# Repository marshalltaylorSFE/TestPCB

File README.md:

# TestPCB
Repo for various eagle projects

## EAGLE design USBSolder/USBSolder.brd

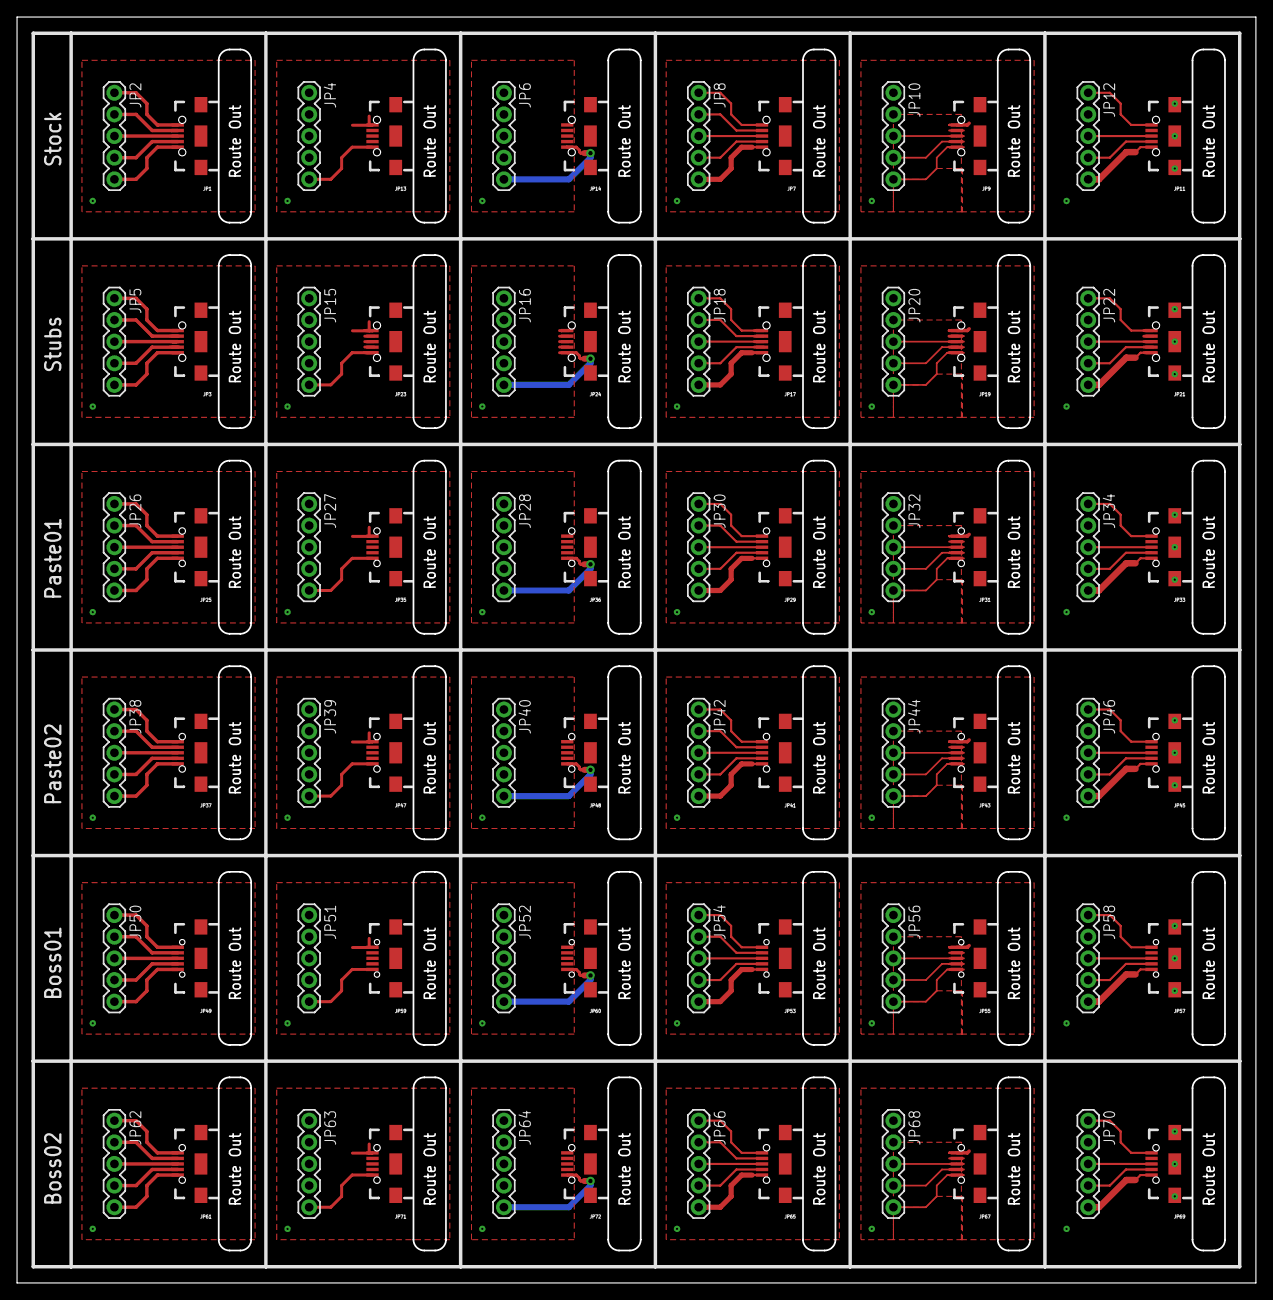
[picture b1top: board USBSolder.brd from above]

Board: 2 copper layers, 145.4 x 148.6 mm, 73 parts (0 on the bottom side), 108 nets.

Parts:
FRAME1: FRAME-LETTER; CREATIVE_COMMONS
JP1, JP7, JP9, JP11, JP13, JP14: USB-B-MICRO-SMD_V03
JP2, JP4, JP5, JP6, JP8, JP10, JP12, JP15, JP16, JP18, JP20, JP22, JP26, JP27, JP28, JP30, JP32, JP34, JP38, JP39, JP40, JP42, JP44, JP46, JP50, JP51, JP52, JP54, JP56, JP58, JP62, JP63, JP64, JP66, JP68, JP70: 1X05
JP3, JP17, JP19, JP21, JP23, JP24: USB-MICRO-STUBS-01
JP25, JP29, JP31, JP33, JP35, JP36: USB-MICRO-PASTE-01
JP37, JP41, JP43, JP45, JP47, JP48: USB-MICRO-PASTE-02
JP49, JP53, JP55, JP57, JP59, JP60: USB-MICRO-BOSS-01
JP61, JP65, JP67, JP69, JP71, JP72: USB-MICRO-BOSS-02

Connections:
5V1: JP6.5, JP14.VBUS1
5V2: JP16.5, JP24.VBUS1
5V3: JP28.5, JP36.VBUS1
5V4: JP40.5, JP48.VBUS1
5V5: JP52.5, JP60.VBUS1
5V6: JP64.5, JP72.VBUS1
GND: JP1.SHIELD1, JP1.SHIELD2, JP1.SHIELD3, JP4.1, JP6.1, JP7.GND1, JP8.1, JP9.GND1, JP10.1, JP11.GND1, JP11.SHIELD1, JP11.SHIELD2, JP11.SHIELD3, JP12.1, JP13.GND1, JP14.GND1
GND1: JP3.SHIELD1, JP3.SHIELD2, JP3.SHIELD3, JP15.1, JP16.1, JP17.GND1, JP18.1, JP19.GND1, JP20.1, JP21.GND1, JP21.SHIELD1, JP21.SHIELD2, JP21.SHIELD3, JP22.1, JP23.GND1, JP24.GND1
GND2: JP25.SHIELD1, JP25.SHIELD2, JP25.SHIELD3, JP27.1, JP28.1, JP29.GND1, JP30.1, JP31.GND1, JP32.1, JP33.GND1, JP33.SHIELD1, JP33.SHIELD2, JP33.SHIELD3, JP34.1, JP35.GND1, JP36.GND1
GND3: JP37.SHIELD1, JP37.SHIELD2, JP37.SHIELD3, JP39.1, JP40.1, JP41.GND1, JP42.1, JP43.GND1, JP44.1, JP45.GND1, JP45.SHIELD1, JP45.SHIELD2, JP45.SHIELD3, JP46.1, JP47.GND1, JP48.GND1
GND4: JP49.SHIELD1, JP49.SHIELD2, JP49.SHIELD3, JP51.1, JP52.1, JP53.GND1, JP54.1, JP55.GND1, JP56.1, JP57.GND1, JP57.SHIELD1, JP57.SHIELD2, JP57.SHIELD3, JP58.1, JP59.GND1, JP60.GND1
GND5: JP61.SHIELD1, JP61.SHIELD2, JP61.SHIELD3, JP63.1, JP64.1, JP65.GND1, JP66.1, JP67.GND1, JP68.1, JP69.GND1, JP69.SHIELD1, JP69.SHIELD2, JP69.SHIELD3, JP70.1, JP71.GND1, JP72.GND1
unnamed: JP1.GND1, JP2.1
unnamed: JP1.ID1, JP2.2
unnamed: JP1.D+1, JP2.3
unnamed: JP1.D-1, JP2.4
unnamed: JP1.VBUS1, JP2.5
unnamed: JP3.GND1, JP5.1
unnamed: JP3.ID1, JP5.2
unnamed: JP7.ID1, JP8.2
unnamed: JP4.5, JP13.VBUS1
unnamed: JP7.D+1, JP8.3
unnamed: JP7.D-1, JP8.4
unnamed: JP7.VBUS1, JP8.5
unnamed: JP3.D+1, JP5.3
unnamed: JP3.D-1, JP5.4
unnamed: JP9.D+1, JP10.3
unnamed: JP9.D-1, JP10.4
unnamed: JP9.VBUS1, JP10.5
unnamed: JP3.VBUS1, JP5.5
unnamed: JP15.5, JP23.VBUS1
unnamed: JP11.D+1, JP12.3
unnamed: JP11.D-1, JP12.4
unnamed: JP11.VBUS1, JP12.5
unnamed: JP17.ID1, JP18.2
unnamed: JP17.D+1, JP18.3
unnamed: JP17.D-1, JP18.4
unnamed: JP17.VBUS1, JP18.5
unnamed: JP19.D+1, JP20.3
unnamed: JP19.D-1, JP20.4
unnamed: JP19.VBUS1, JP20.5
unnamed: JP21.D+1, JP22.3
unnamed: JP21.D-1, JP22.4
unnamed: JP21.VBUS1, JP22.5
unnamed: JP25.GND1, JP26.1
unnamed: JP25.ID1, JP26.2
unnamed: JP25.D+1, JP26.3
unnamed: JP25.D-1, JP26.4
unnamed: JP25.VBUS1, JP26.5
unnamed: JP27.5, JP35.VBUS1
unnamed: JP29.ID1, JP30.2
unnamed: JP29.D+1, JP30.3
unnamed: JP29.D-1, JP30.4
unnamed: JP29.VBUS1, JP30.5
unnamed: JP31.D+1, JP32.3
unnamed: JP31.D-1, JP32.4
unnamed: JP31.VBUS1, JP32.5
unnamed: JP33.D+1, JP34.3
unnamed: JP33.D-1, JP34.4
unnamed: JP33.VBUS1, JP34.5
unnamed: JP37.GND1, JP38.1
unnamed: JP37.ID1, JP38.2
unnamed: JP37.D+1, JP38.3
unnamed: JP37.D-1, JP38.4
unnamed: JP37.VBUS1, JP38.5
unnamed: JP39.5, JP47.VBUS1
unnamed: JP41.ID1, JP42.2
unnamed: JP41.D+1, JP42.3
unnamed: JP41.D-1, JP42.4
unnamed: JP41.VBUS1, JP42.5
unnamed: JP43.D+1, JP44.3
unnamed: JP43.D-1, JP44.4
unnamed: JP43.VBUS1, JP44.5
unnamed: JP45.D+1, JP46.3
unnamed: JP45.D-1, JP46.4
unnamed: JP45.VBUS1, JP46.5
unnamed: JP49.GND1, JP50.1
unnamed: JP49.ID1, JP50.2
unnamed: JP49.D+1, JP50.3
unnamed: JP49.D-1, JP50.4
unnamed: JP49.VBUS1, JP50.5
unnamed: JP51.5, JP59.VBUS1
unnamed: JP53.ID1, JP54.2
unnamed: JP53.D+1, JP54.3
unnamed: JP53.D-1, JP54.4
unnamed: JP53.VBUS1, JP54.5
unnamed: JP55.D+1, JP56.3
unnamed: JP55.D-1, JP56.4
unnamed: JP55.VBUS1, JP56.5
unnamed: JP57.D+1, JP58.3
unnamed: JP57.D-1, JP58.4
unnamed: JP57.VBUS1, JP58.5
unnamed: JP61.GND1, JP62.1
unnamed: JP61.ID1, JP62.2
unnamed: JP61.D+1, JP62.3
unnamed: JP61.D-1, JP62.4
unnamed: JP61.VBUS1, JP62.5
unnamed: JP63.5, JP71.VBUS1
unnamed: JP65.ID1, JP66.2
unnamed: JP65.D+1, JP66.3
unnamed: JP65.D-1, JP66.4
unnamed: JP65.VBUS1, JP66.5
unnamed: JP67.D+1, JP68.3
unnamed: JP67.D-1, JP68.4
unnamed: JP67.VBUS1, JP68.5
unnamed: JP69.D+1, JP70.3
unnamed: JP69.D-1, JP70.4
unnamed: JP69.VBUS1, JP70.5

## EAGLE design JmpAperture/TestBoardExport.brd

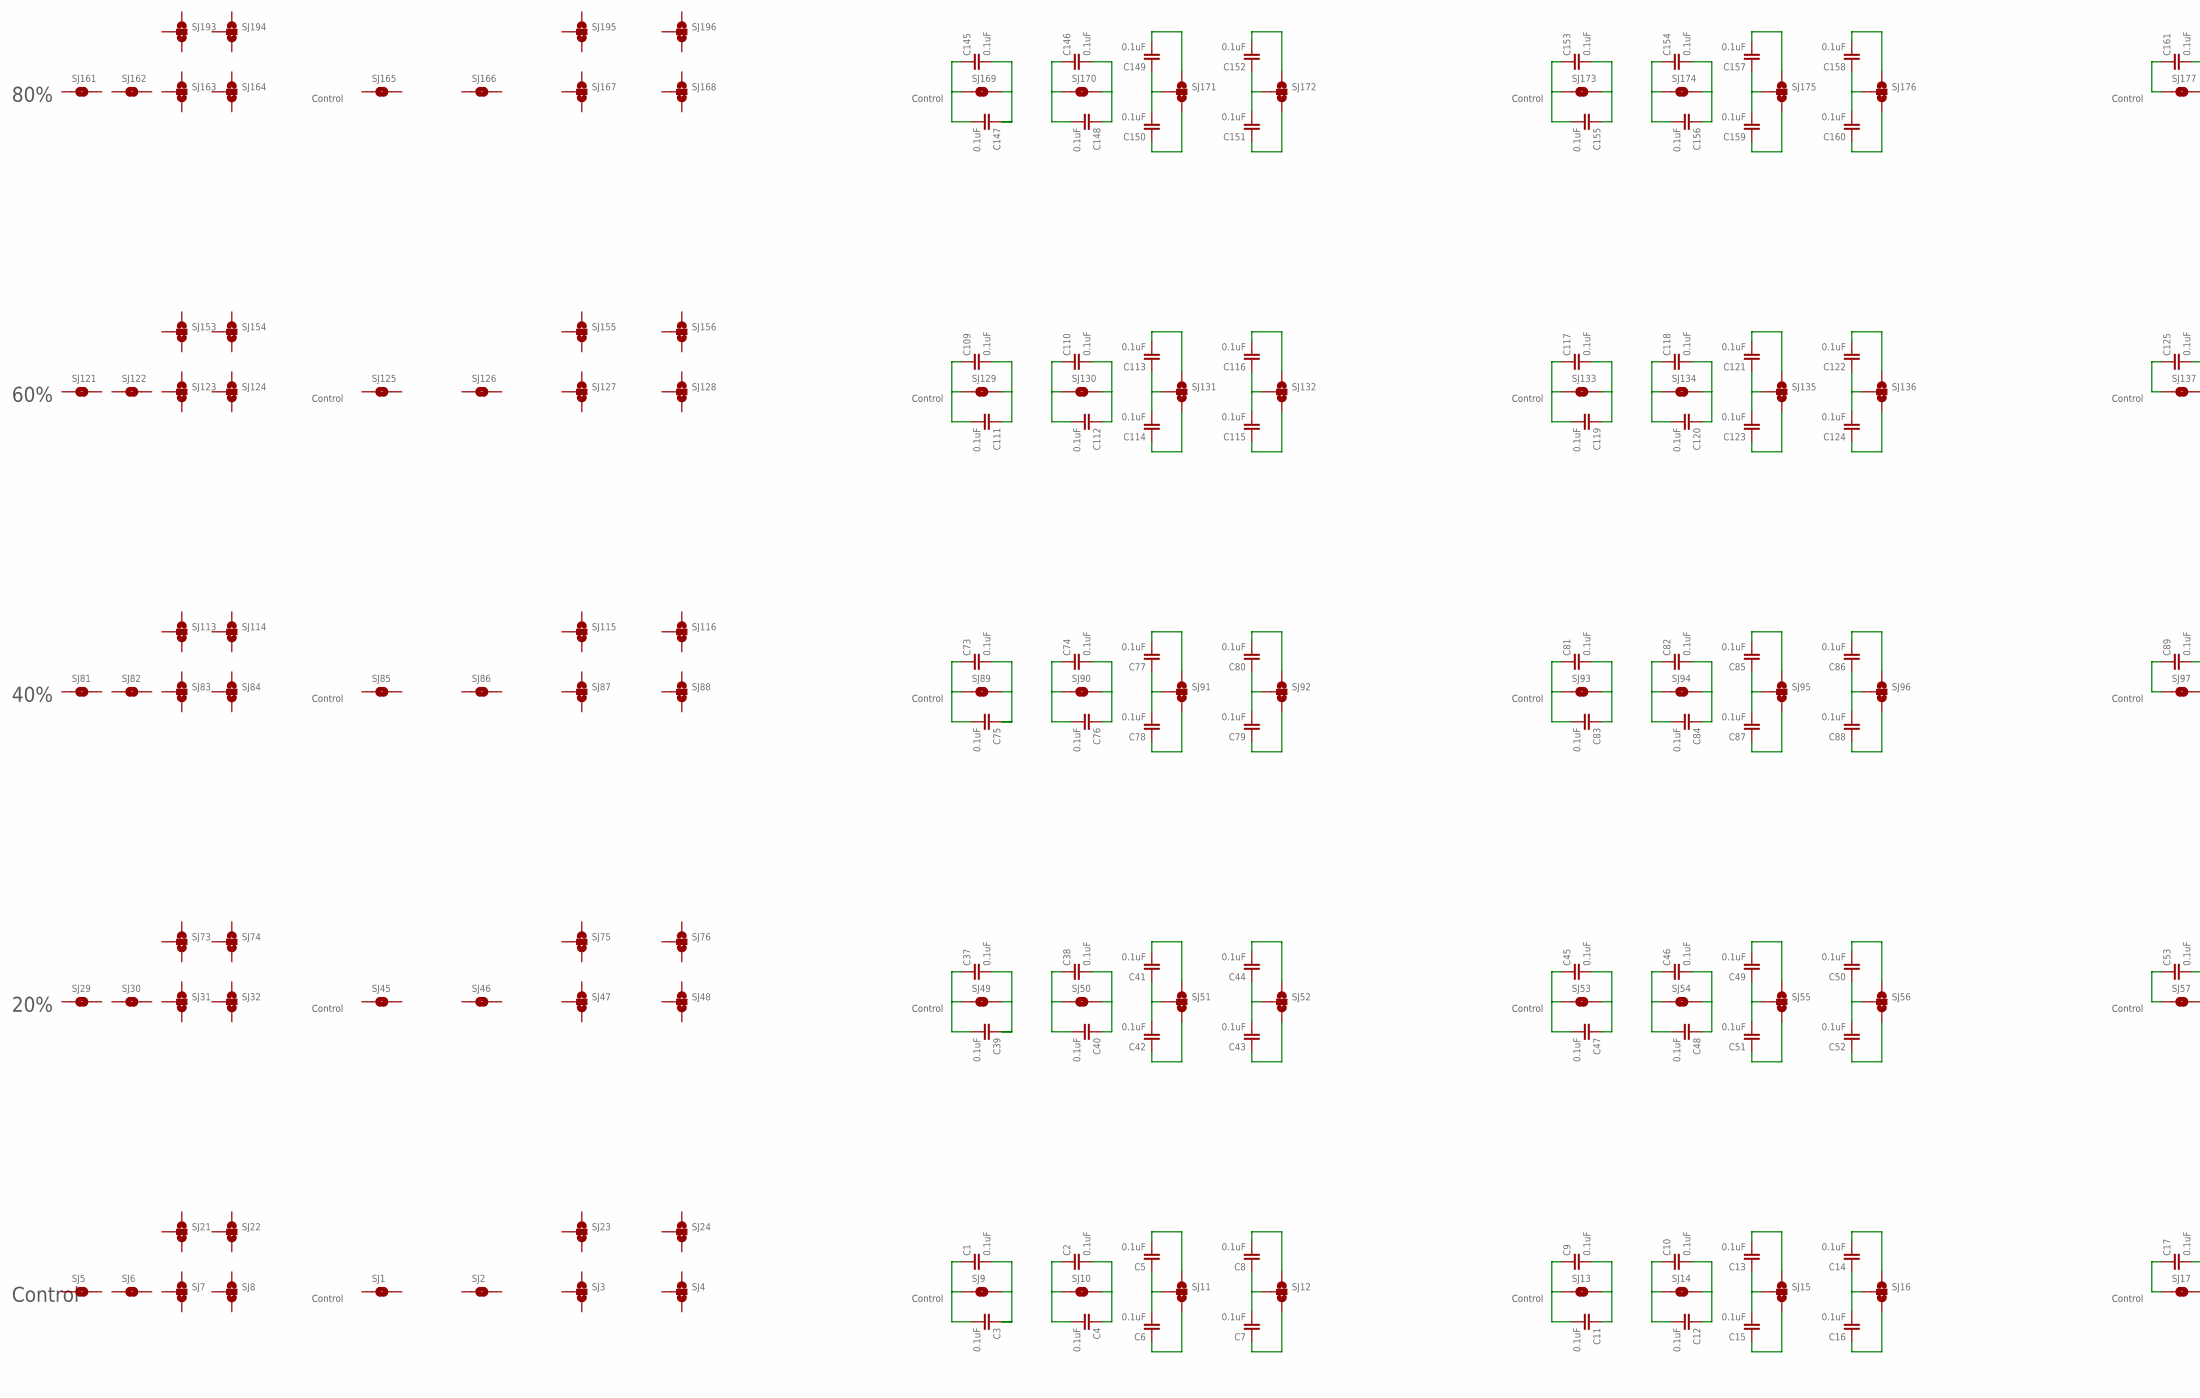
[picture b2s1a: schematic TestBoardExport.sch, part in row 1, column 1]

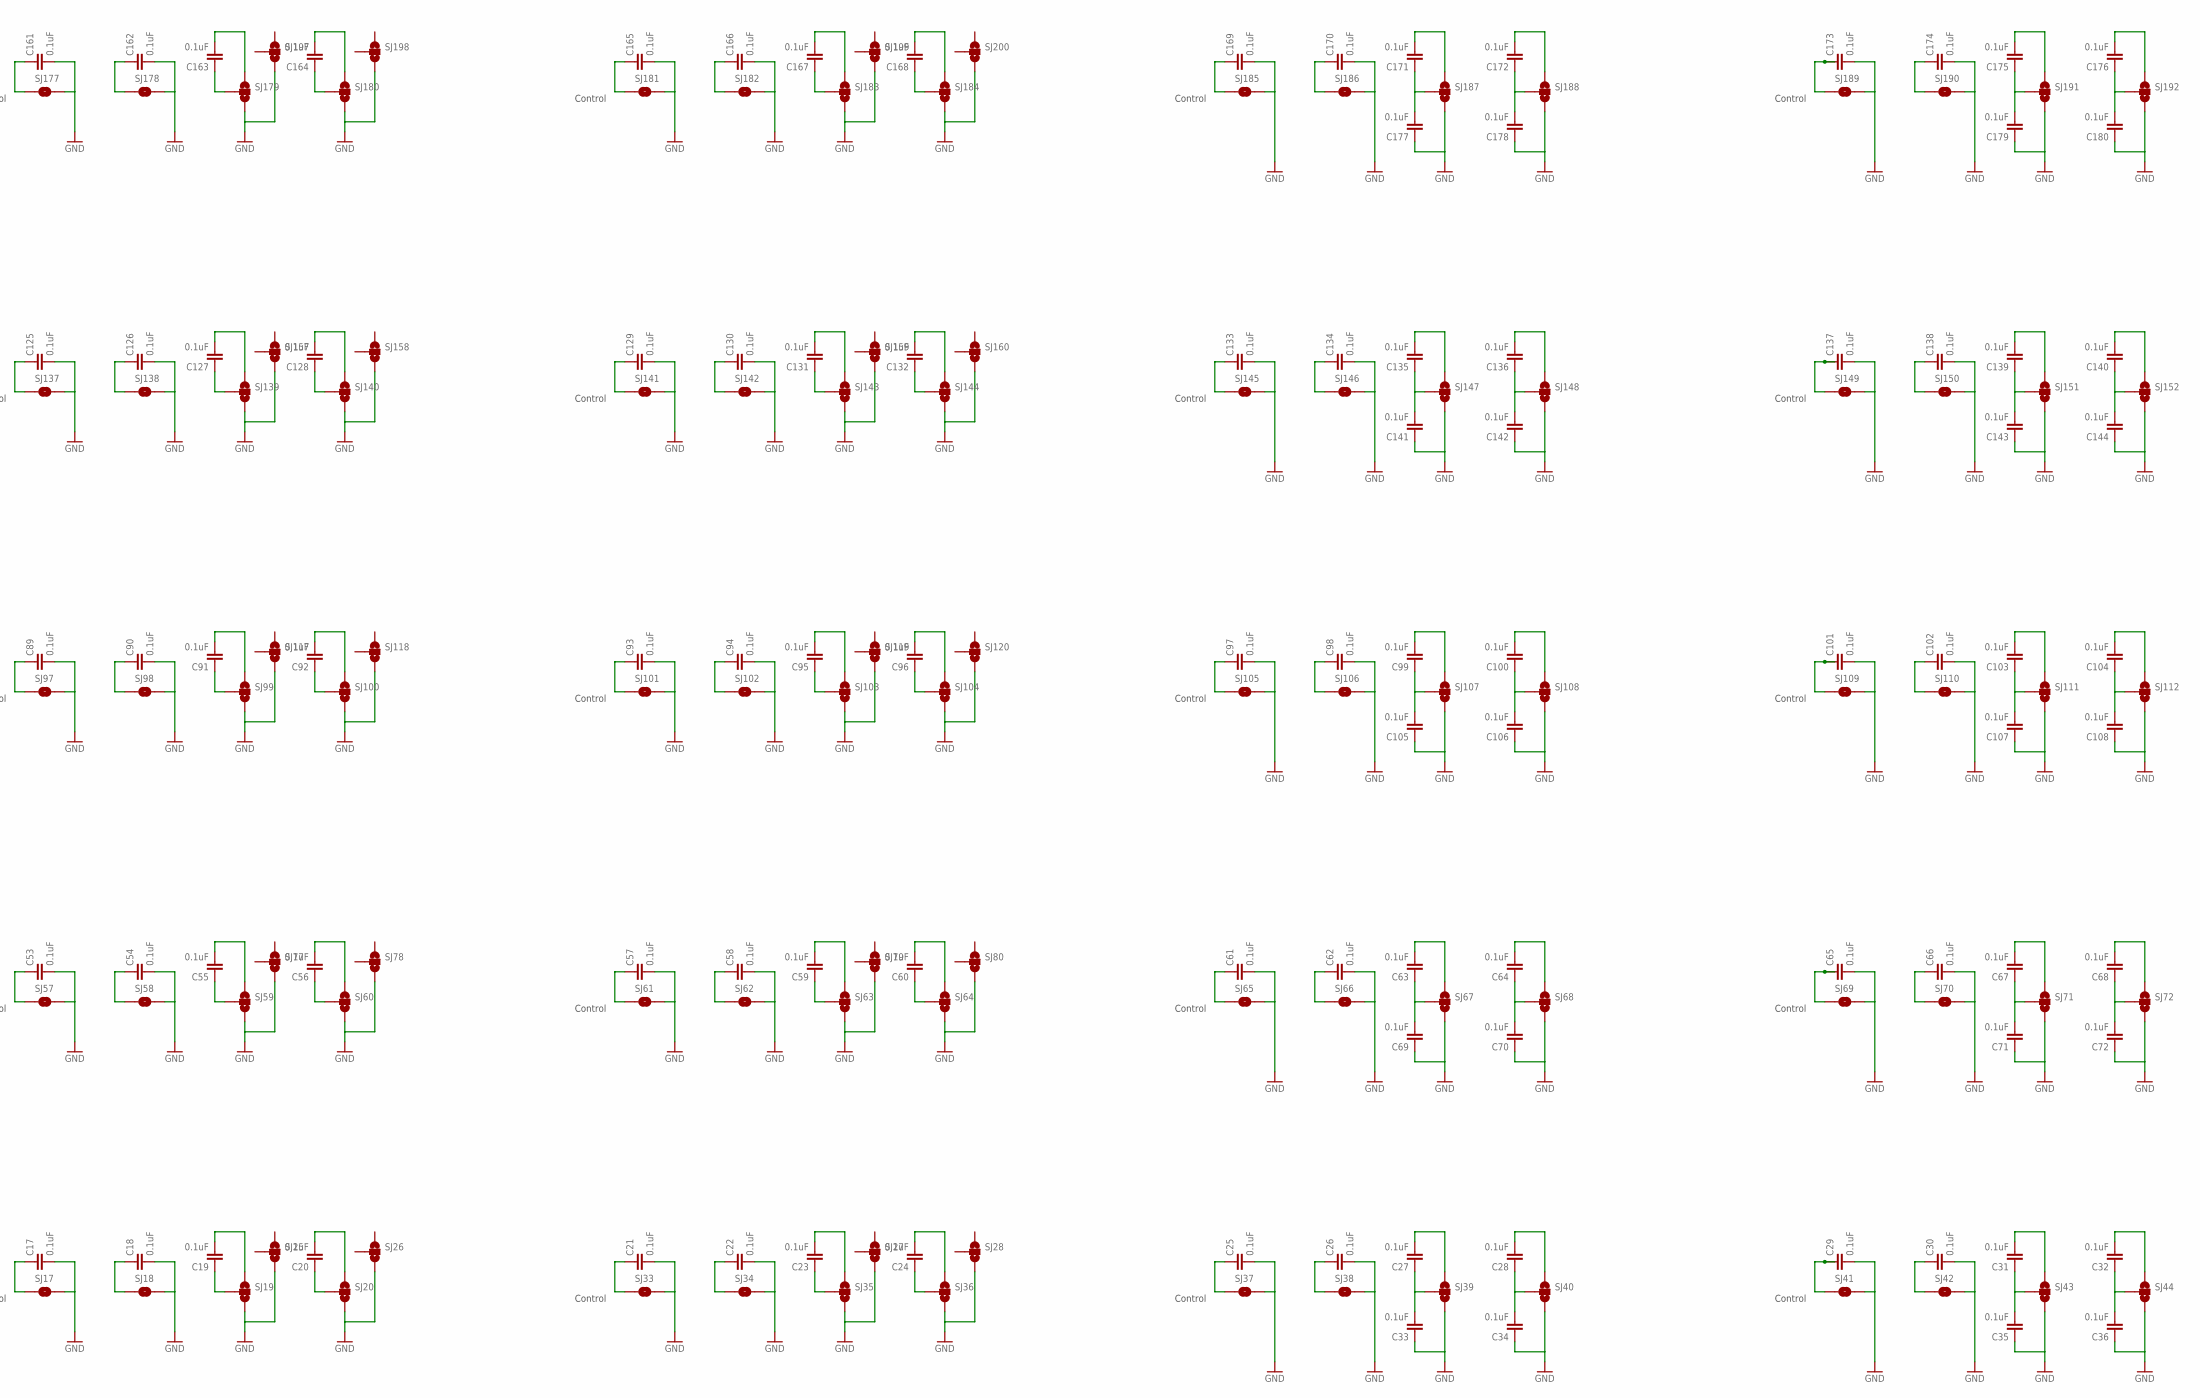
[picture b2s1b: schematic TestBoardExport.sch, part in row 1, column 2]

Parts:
C1, C2, C3, C4, C5, C6, C7, C8, C9, C10, C11, C12, C13, C14, C15, C16, C17, C18, C19, C20, C21, C22, C23, C24, C25, C26, C27, C28, C29, C30, C31, C32, C33, C34, C35, C36, C37, C38, C39, C40, C41, C42, C43, C44, C45, C46, C47, C48, C49, C50, C51, C52, C53, C54, C55, C56, C57, C58, C59, C60, C61, C62, C63, C64, C65, C66, C67, C68, C69, C70, C71, C72, C73, C74, C75, C76, C77, C78, C79, C80, C81, C82, C83, C84, C85, C86, C87, C88, C89, C90, C91, C92, C93, C94, C95, C96, C97, C98, C99, C100, C101, C102, C103, C104, C105, C106, C107, C108, C109, C110, C111, C112, C113, C114, C115, C116, C117, C118, C119, C120, C121, C122, C123, C124, C125, C126, C127, C128, C129, C130, C131, C132, C133, C134, C135, C136, C137, C138, C139, C140, C141, C142, C143, C144, C145, C146, C147, C148, C149, C150, C151, C152, C153, C154, C155, C156, C157, C158, C159, C160, C161, C162, C163, C164, C165, C166, C167, C168, C169, C170, C171, C172, C173, C174, C175, C176, C177, C178, C179, C180: 0.1uF; 0603-CAP
SJ1, SJ2, SJ5, SJ6, SJ9, SJ10, SJ13, SJ14, SJ17, SJ18, SJ33, SJ34, SJ37, SJ38, SJ41, SJ42, SJ69, SJ70: JUMPER-PAD-2-NO; PAD-JUMPER-2-NO_NO_SILK
SJ3, SJ4, SJ7, SJ8, SJ11, SJ12, SJ15, SJ16, SJ19, SJ20, SJ35, SJ36, SJ39, SJ40, SJ43, SJ44: JUMPER-PAD-3-NOYES_SILK; PAD-JUMPER-3-NO_YES_SILK
SJ21, SJ22, SJ23, SJ24, SJ25, SJ26, SJ27, SJ28: JUMPER-PAD-3-NO3_0; PAD-JUMPER-3-NO_YES_SILK_ALL
SJ29, SJ30, SJ45, SJ46, SJ49, SJ50, SJ53, SJ54, SJ57, SJ58, SJ61, SJ62, SJ65, SJ66: JUMPER-PAD-2-NO20; PAD-JUMPER-2-NO_NO_SILK_20
SJ31, SJ32, SJ47, SJ48, SJ51, SJ52, SJ55, SJ56, SJ59, SJ60, SJ63, SJ64, SJ67, SJ68, SJ71, SJ72: JUMPER-PAD-3-NO2_20; PAD-JUMPER-3-NO_YES_SILK_20
SJ73, SJ74, SJ75, SJ76, SJ77, SJ78, SJ79, SJ80: JUMPER-PAD-3-NO3_20; PAD-JUMPER-3-NO_YES_SILK_ALL_20
SJ81, SJ82, SJ85, SJ86, SJ89, SJ90, SJ93, SJ94, SJ97, SJ98, SJ101, SJ102, SJ105, SJ106, SJ109, SJ110: JUMPER-PAD-2-NO40; PAD-JUMPER-2-NO_NO_SILK_40
SJ83, SJ84, SJ87, SJ88, SJ91, SJ92, SJ95, SJ96, SJ99, SJ100, SJ103, SJ104, SJ107, SJ108, SJ111, SJ112: JUMPER-PAD-3-NO2_40; PAD-JUMPER-3-NO_YES_SILK_40
SJ113, SJ114, SJ115, SJ116, SJ117, SJ118, SJ119, SJ120: JUMPER-PAD-3-NO3_40; PAD-JUMPER-3-NO_YES_SILK_ALL_40
SJ121, SJ122, SJ125, SJ126, SJ129, SJ130, SJ133, SJ134, SJ137, SJ138, SJ141, SJ142, SJ145, SJ146, SJ149, SJ150: JUMPER-PAD-2-NO60; PAD-JUMPER-2-NO_NO_SILK_60
SJ123, SJ124, SJ127, SJ128, SJ131, SJ132, SJ135, SJ136, SJ139, SJ140, SJ143, SJ144, SJ147, SJ148, SJ151, SJ152: JUMPER-PAD-3-NO2_60; PAD-JUMPER-3-NO_YES_SILK_60
SJ153, SJ154, SJ155, SJ156, SJ157, SJ158, SJ159, SJ160: JUMPER-PAD-3-NO3_60; PAD-JUMPER-3-NO_YES_SILK_ALL_60
SJ161, SJ162, SJ165, SJ166, SJ169, SJ170, SJ173, SJ174, SJ177, SJ178, SJ181, SJ182, SJ185, SJ186, SJ189, SJ190: JUMPER-PAD-2-NO80; PAD-JUMPER-2-NO_NO_SILK_80
SJ163, SJ164, SJ167, SJ168, SJ171, SJ172, SJ175, SJ176, SJ179, SJ180, SJ183, SJ184, SJ187, SJ188, SJ191, SJ192: JUMPER-PAD-3-NO2_80; PAD-JUMPER-3-NO_YES_SILK_80
SJ193, SJ194, SJ195, SJ196, SJ197, SJ198, SJ199, SJ200: JUMPER-PAD-3-NO3_80; PAD-JUMPER-3-NO_YES_SILK_ALL_80

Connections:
GND: C17.2, C18.2, C21.2, C22.2, C25.2, C26.2, C29.2, C30.2, C33.1, C34.1, C35.1, C36.1, C53.2, C54.2, C57.2, C58.2, C61.2, C62.2, C65.2, C66.2, C69.1, C70.1, C71.1, C72.1, C89.2, C90.2, C93.2, C94.2, C97.2, C98.2, C101.2, C102.2, C105.1, C106.1, C107.1, C108.1, C125.2, C126.2, C129.2, C130.2, C133.2, C134.2, C137.2, C138.2, C141.1, C142.1, C143.1, C144.1, C161.2, C162.2, C165.2, C166.2, C169.2, C170.2, C173.2, C174.2, C177.1, C178.1, C179.1, C180.1, SJ17.2, SJ18.2, SJ19.3, SJ20.3, SJ25.3, SJ26.3, SJ27.3, SJ28.3, SJ33.2, SJ34.2, SJ35.3, SJ36.3, SJ37.2, SJ38.2, SJ39.3, SJ40.3, SJ41.2, SJ42.2, SJ43.3, SJ44.3, SJ57.2, SJ58.2, SJ59.3, SJ60.3, SJ61.2, SJ62.2, SJ63.3, SJ64.3, SJ65.2, SJ66.2, SJ67.3, SJ68.3, SJ69.2, SJ70.2, SJ71.3, SJ72.3, SJ77.3, SJ78.3, SJ79.3, SJ80.3, SJ97.2, SJ98.2, SJ99.3, SJ100.3, SJ101.2, SJ102.2, SJ103.3, SJ104.3, SJ105.2, SJ106.2, SJ107.3, SJ108.3, SJ109.2, SJ110.2, SJ111.3, SJ112.3, SJ117.3, SJ118.3, SJ119.3, SJ120.3, SJ137.2, SJ138.2, SJ139.3, SJ140.3, SJ141.2, SJ142.2, SJ143.3, SJ144.3, SJ145.2, SJ146.2, SJ147.3, SJ148.3, SJ149.2, SJ150.2, SJ151.3, SJ152.3, SJ157.3, SJ158.3, SJ159.3, SJ160.3, SJ177.2, SJ178.2, SJ179.3, SJ180.3, SJ181.2, SJ182.2, SJ183.3, SJ184.3, SJ185.2, SJ186.2, SJ187.3, SJ188.3, SJ189.2, SJ190.2, SJ191.3, SJ192.3, SJ197.3, SJ198.3, SJ199.3, SJ200.3
unnamed: C1.1, C3.2, SJ9.1
unnamed: C1.2, C3.1, SJ9.2
unnamed: C2.1, C4.2, SJ10.1
unnamed: C2.2, C4.1, SJ10.2
unnamed: C5.1, C6.2, SJ11.2
unnamed: C5.2, SJ11.1
unnamed: C6.1, SJ11.3
unnamed: C7.2, C8.1, SJ12.2
unnamed: C8.2, SJ12.1
unnamed: C7.1, SJ12.3
unnamed: C10.2, C12.1, SJ14.2
unnamed: C10.1, C12.2, SJ14.1
unnamed: C9.1, C11.2, SJ13.1
unnamed: C9.2, C11.1, SJ13.2
unnamed: C13.1, C15.2, SJ15.2
unnamed: C13.2, SJ15.1
unnamed: C15.1, SJ15.3
unnamed: C14.1, C16.2, SJ16.2
unnamed: C14.2, SJ16.1
unnamed: C16.1, SJ16.3
unnamed: C17.1, SJ17.1
unnamed: C18.1, SJ18.1
unnamed: C37.1, C39.2, SJ49.1
unnamed: C19.1, SJ19.2
unnamed: C19.2, SJ19.1
unnamed: C20.1, SJ20.2
unnamed: C20.2, SJ20.1
unnamed: C21.1, SJ33.1
unnamed: C37.2, C39.1, SJ49.2
unnamed: C22.1, SJ34.1
unnamed: C23.1, SJ35.2
unnamed: C23.2, SJ35.1
unnamed: C24.2, SJ36.1
unnamed: C24.1, SJ36.2
unnamed: C25.1, SJ37.1
unnamed: C38.1, C40.2, SJ50.1
unnamed: C26.1, SJ38.1
unnamed: C38.2, C40.1, SJ50.2
unnamed: C27.1, C33.2, SJ39.2
unnamed: C27.2, SJ39.1
unnamed: C41.1, C42.2, SJ51.2
unnamed: C28.1, C34.2, SJ40.2
unnamed: C28.2, SJ40.1
unnamed: C41.2, SJ51.1
unnamed: C29.1, SJ41.1
unnamed: C42.1, SJ51.3
unnamed: C30.1, SJ42.1
unnamed: C43.2, C44.1, SJ52.2
unnamed: C31.1, C35.2, SJ43.2
unnamed: C31.2, SJ43.1
unnamed: C32.1, C36.2, SJ44.2
unnamed: C32.2, SJ44.1
unnamed: C44.2, SJ52.1
unnamed: C43.1, SJ52.3
unnamed: C46.2, C48.1, SJ54.2
unnamed: C46.1, C48.2, SJ54.1
unnamed: C45.1, C47.2, SJ53.1
unnamed: C45.2, C47.1, SJ53.2
unnamed: C49.1, C51.2, SJ55.2
unnamed: C49.2, SJ55.1
unnamed: C51.1, SJ55.3
unnamed: C50.1, C52.2, SJ56.2
unnamed: C50.2, SJ56.1
unnamed: C52.1, SJ56.3
unnamed: C53.1, SJ57.1
unnamed: C54.1, SJ58.1
unnamed: C55.1, SJ59.2
unnamed: C55.2, SJ59.1
unnamed: C56.1, SJ60.2
unnamed: C56.2, SJ60.1
unnamed: C57.1, SJ61.1
unnamed: C58.1, SJ62.1
unnamed: C59.1, SJ63.2
unnamed: C59.2, SJ63.1
unnamed: C60.2, SJ64.1
unnamed: C60.1, SJ64.2
unnamed: C61.1, SJ65.1
unnamed: C62.1, SJ66.1
unnamed: C63.1, C69.2, SJ67.2
unnamed: C63.2, SJ67.1
unnamed: C64.1, C70.2, SJ68.2
unnamed: C64.2, SJ68.1
unnamed: C65.1, SJ69.1
unnamed: C66.1, SJ70.1
unnamed: C67.1, C71.2, SJ71.2
unnamed: C67.2, SJ71.1
unnamed: C68.1, C72.2, SJ72.2
unnamed: C68.2, SJ72.1
unnamed: C73.1, C75.2, SJ89.1
unnamed: C73.2, C75.1, SJ89.2
unnamed: C74.1, C76.2, SJ90.1
unnamed: C74.2, C76.1, SJ90.2
unnamed: C77.1, C78.2, SJ91.2
unnamed: C77.2, SJ91.1
unnamed: C78.1, SJ91.3
unnamed: C79.2, C80.1, SJ92.2
unnamed: C80.2, SJ92.1
unnamed: C79.1, SJ92.3
unnamed: C82.2, C84.1, SJ94.2
unnamed: C82.1, C84.2, SJ94.1
unnamed: C81.1, C83.2, SJ93.1
unnamed: C81.2, C83.1, SJ93.2
unnamed: C85.1, C87.2, SJ95.2
unnamed: C85.2, SJ95.1
unnamed: C87.1, SJ95.3
unnamed: C86.1, C88.2, SJ96.2
unnamed: C86.2, SJ96.1
unnamed: C88.1, SJ96.3
unnamed: C89.1, SJ97.1
unnamed: C90.1, SJ98.1
unnamed: C91.1, SJ99.2
unnamed: C91.2, SJ99.1
unnamed: C92.1, SJ100.2
unnamed: C92.2, SJ100.1
unnamed: C93.1, SJ101.1
unnamed: C94.1, SJ102.1
unnamed: C95.1, SJ103.2
unnamed: C95.2, SJ103.1
unnamed: C96.2, SJ104.1
unnamed: C96.1, SJ104.2
unnamed: C97.1, SJ105.1
unnamed: C98.1, SJ106.1
unnamed: C99.1, C105.2, SJ107.2
unnamed: C99.2, SJ107.1
unnamed: C100.1, C106.2, SJ108.2
unnamed: C100.2, SJ108.1
unnamed: C101.1, SJ109.1
unnamed: C102.1, SJ110.1
unnamed: C103.1, C107.2, SJ111.2
unnamed: C103.2, SJ111.1
unnamed: C104.1, C108.2, SJ112.2
unnamed: C104.2, SJ112.1
unnamed: C109.1, C111.2, SJ129.1
unnamed: C109.2, C111.1, SJ129.2
unnamed: C110.1, C112.2, SJ130.1
unnamed: C110.2, C112.1, SJ130.2
unnamed: C113.1, C114.2, SJ131.2
unnamed: C113.2, SJ131.1
unnamed: C114.1, SJ131.3
unnamed: C115.2, C116.1, SJ132.2
unnamed: C116.2, SJ132.1
unnamed: C115.1, SJ132.3
unnamed: C118.2, C120.1, SJ134.2
unnamed: C118.1, C120.2, SJ134.1
unnamed: C117.1, C119.2, SJ133.1
unnamed: C117.2, C119.1, SJ133.2
unnamed: C121.1, C123.2, SJ135.2
unnamed: C121.2, SJ135.1
unnamed: C123.1, SJ135.3
unnamed: C122.1, C124.2, SJ136.2
unnamed: C122.2, SJ136.1
unnamed: C124.1, SJ136.3
unnamed: C125.1, SJ137.1
unnamed: C126.1, SJ138.1
unnamed: C127.1, SJ139.2
unnamed: C127.2, SJ139.1
unnamed: C128.1, SJ140.2
unnamed: C128.2, SJ140.1
unnamed: C129.1, SJ141.1
unnamed: C130.1, SJ142.1
unnamed: C131.1, SJ143.2
unnamed: C131.2, SJ143.1
unnamed: C132.2, SJ144.1
unnamed: C132.1, SJ144.2
unnamed: C133.1, SJ145.1
unnamed: C134.1, SJ146.1
unnamed: C135.1, C141.2, SJ147.2
unnamed: C135.2, SJ147.1
unnamed: C136.1, C142.2, SJ148.2
unnamed: C136.2, SJ148.1
unnamed: C137.1, SJ149.1
unnamed: C138.1, SJ150.1
unnamed: C139.1, C143.2, SJ151.2
unnamed: C139.2, SJ151.1
unnamed: C140.1, C144.2, SJ152.2
unnamed: C140.2, SJ152.1
unnamed: C145.1, C147.2, SJ169.1
unnamed: C145.2, C147.1, SJ169.2
unnamed: C146.1, C148.2, SJ170.1
unnamed: C146.2, C148.1, SJ170.2
unnamed: C149.1, C150.2, SJ171.2
unnamed: C149.2, SJ171.1
unnamed: C150.1, SJ171.3
unnamed: C151.2, C152.1, SJ172.2
unnamed: C152.2, SJ172.1
unnamed: C151.1, SJ172.3
unnamed: C154.2, C156.1, SJ174.2
unnamed: C154.1, C156.2, SJ174.1
unnamed: C153.1, C155.2, SJ173.1
unnamed: C153.2, C155.1, SJ173.2
unnamed: C157.1, C159.2, SJ175.2
unnamed: C157.2, SJ175.1
unnamed: C159.1, SJ175.3
unnamed: C158.1, C160.2, SJ176.2
unnamed: C158.2, SJ176.1
unnamed: C160.1, SJ176.3
unnamed: C161.1, SJ177.1
unnamed: C162.1, SJ178.1
unnamed: C163.1, SJ179.2
unnamed: C163.2, SJ179.1
unnamed: C164.1, SJ180.2
unnamed: C164.2, SJ180.1
unnamed: C165.1, SJ181.1
unnamed: C166.1, SJ182.1
unnamed: C167.1, SJ183.2
unnamed: C167.2, SJ183.1
unnamed: C168.2, SJ184.1
unnamed: C168.1, SJ184.2
unnamed: C169.1, SJ185.1
unnamed: C170.1, SJ186.1
unnamed: C171.1, C177.2, SJ187.2
unnamed: C171.2, SJ187.1
unnamed: C172.1, C178.2, SJ188.2
unnamed: C172.2, SJ188.1
unnamed: C173.1, SJ189.1
unnamed: C174.1, SJ190.1
unnamed: C175.1, C179.2, SJ191.2
unnamed: C175.2, SJ191.1
unnamed: C176.1, C180.2, SJ192.2
unnamed: C176.2, SJ192.1

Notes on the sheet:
Control
20%
40%
60%
80%

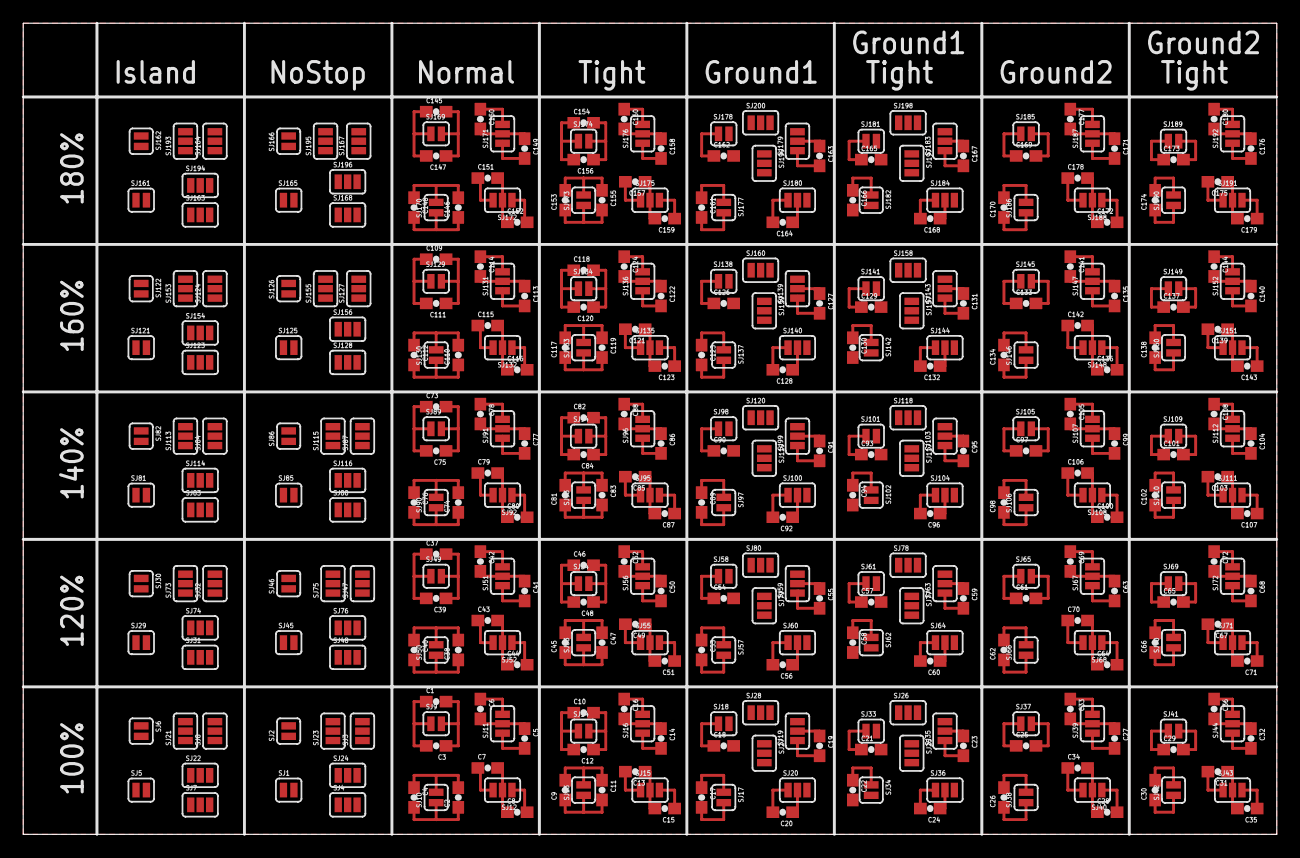
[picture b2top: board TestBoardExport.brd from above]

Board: 2 copper layers, 107.9 x 69.8 mm, 380 parts (0 on the bottom side), 221 nets.

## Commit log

2015-06-17 added libs, made project
2015-06-24 First row plus footprints
2015-06-24 Initial design complete
2015-06-24 Changed directory name
2015-06-24 touch-ups
2015-08-27 started USB test layouts
2015-08-28 done with usb test
2016-03-18 added example shapes for dfm

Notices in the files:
parts and their libraries:
TestAperatures: Licensing: Creative Commons ShareAlike 4.0 International - https://creativecommons.org/licenses/by-sa/4.0
SparkFun-Aesthetics: Released under the Creative Commons Attribution Share-Alike 4.0 License
SparkFun-Aesthetics: https://creativecommons.org/licenses/by-sa/4.0
